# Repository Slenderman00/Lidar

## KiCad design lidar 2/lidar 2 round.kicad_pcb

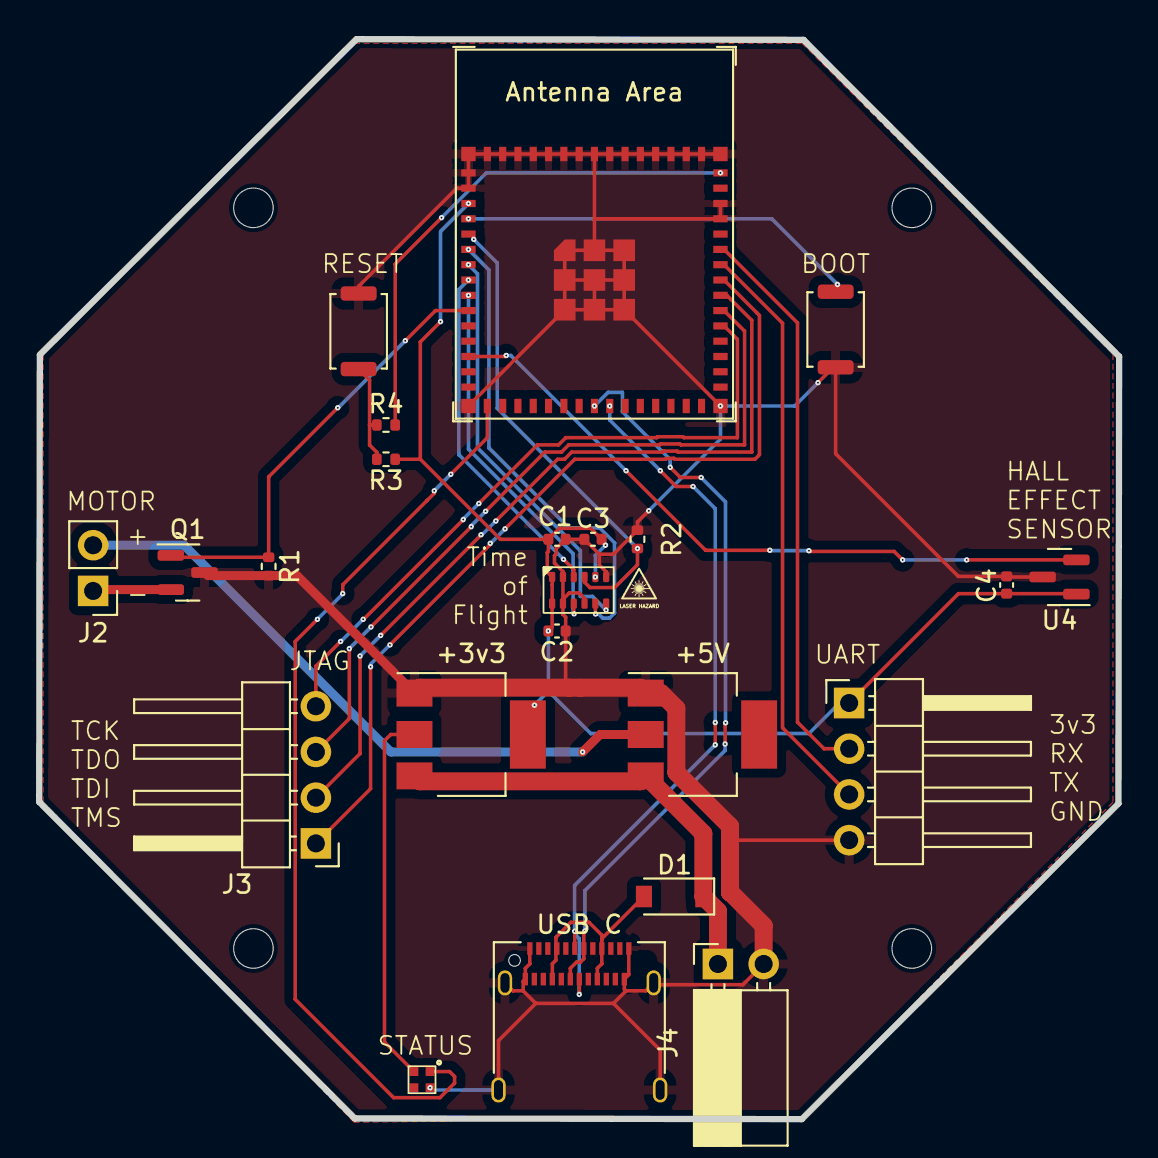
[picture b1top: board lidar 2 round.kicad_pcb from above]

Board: 2 copper layers, 60.0 x 60.0 mm, 27 parts (0 on the bottom side), 25 nets.

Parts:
+3v3: AMS1117-3.3; SOT-223-3_TabPin2
+5V: AMS1117-5.0; SOT-223-3_TabPin2
C1, C2, C3, C4: X7R 0.1 μF 6.3 V; C_0402_1005Metric
D1: MBR0520; D_SOD-123
H1, H2, H3, H5: MountingHole_Pad; MountingHole_2.2mm_M2
J1: UART; PinHeader_1x04_P2.54mm_Horizontal
J2: Motor; PinHeader_1x02_P2.54mm_Vertical
J3: JTAG; PinHeader_1x04_P2.54mm_Horizontal
J4: VIN; PinSocket_1x02_P2.54mm_Horizontal
Q1: BC847; SOT-23
R1, R2: 1Mohm; R_0402_1005Metric
R3, R4: 1 Mohm; R_0402_1005Metric
SW1: BOOT; SW_Push_SPST_NO_Alps_SKRK
SW2: RESET; SW_Push_SPST_NO_Alps_SKRK
U2: TMF8805
U3: LC8805B-1515
U4: DRV5055A2xDBZxQ1; SOT-23
U5: ESP32-S3-MINI-1
USB C: USB_C_Receptacle_USB2.0; USB_C_Receptacle_Amphenol_12401610E4-2A

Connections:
+3.3V: +3v3.2 (VO), C1.2, C2.2, C3.2, C4.2, J1.1, R3.1, U2.1 (VDDV), U2.8 (GND), U2.12 (VDDC), U3.2 (VDD), U4.1 (VCC), U5.3 (3V3)
+5V: +5V.2 (VO), J2.2
D+: U5.24 (GPIO20/U1CTS/ADC2_CH9/CLK_OUT1/USB_D+), USB C.A6 (D+), USB C.B6 (D+)
D-: U5.23 (GPIO19/U1RTS/ADC2_CH8/CLK_OUT2/USB_D-), USB C.A7 (D-), USB C.B7 (D-)
Enable: R2.1, U2.9 (EN), U5.5 (GPIO1/TOUCH1/ADC1_CH0)
Enable_Motor: Q1.1 (B), R1.1, U5.10 (GPIO6/TOUCH6/ADC1_CH5)
GND: +3v3.1 (GND), +5V.1 (GND), C1.1, C2.1, C3.1, C4.1, J1.4, J4.2, Q1.3 (C), R1.2, R2.2, SW1.1, SW2.2, U2.2 (GNDC), U2.4 (INT), U2.7 (VDD), U2.11 (GNDV), U3.4 (GND), U4.3 (GND), U5.1 (GND), U5.2 (GND), U5.42 (GND), U5.43 (GND), U5.46 (GND), U5.47 (GND), U5.48 (GND), U5.49 (GND), U5.50 (GND), U5.51 (GND), U5.52 (GND), U5.53 (GND), U5.54 (GND), U5.55 (GND), U5.56 (GND), U5.57 (GND), U5.58 (GND), U5.59 (GND), U5.60 (GND), U5.61 (GND), U5.62 (GND), U5.63 (GND), U5.64 (GND), U5.65 (GND), USB C.A1 (GND), USB C.A12 (GND), USB C.B1 (GND), USB C.B12 (GND), USB C.S1 (SHIELD)
GPIO0: U2.10 (GPIO1), U5.8 (GPIO4/TOUCH4/ADC1_CH3)
GPIO1: U2.3 (GPIO0), U5.9 (GPIO5/TOUCH5/ADC1_CH4)
Hall_Effect_Sensor: U4.2 (OUT), U5.13 (GPIO9/TOUCH9/ADC1_CH8/FSPIHD/SUBSPIHD)
unnamed: D1.2 (A), USB C.A4 (VBUS), USB C.A9 (VBUS), USB C.B4 (VBUS), USB C.B9 (VBUS)
unnamed: J2.1, Q1.2 (E)
unnamed: R3.2, R4.1, SW2.1
unnamed: R4.2, U5.45 (EN)
unnamed: SW1.2, U5.4 (GPIO0/BOOT)
RX: J1.2, U5.40 (U0RXD/GPIO44/CLK_OUT2)
SCL: U2.5 (SCL), U5.6 (GPIO2/TOUCH2/ADC1_CH1)
SDA: U2.6 (SDA), U5.7 (GPIO3/TOUCH3/ADC1_CH2)
SLED: U3.1 (DIN), U5.16 (GPIO12/TOUCH12/ADC2_CH1/FSPICLK/FSPIIO6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)
TCK: J3.4, U5.35 (MTCK/GPIO39/CLK_OUT3/SUBSPICS1)
TDI: J3.2, U5.37 (MTDI/GPIO41/CLK_OUT1)
TDO: J3.3, U5.36 (MTDO/GPIO40/CLK_OUT2)
TMS: J3.1, U5.38 (MTMS/GPIO42)
TX: J1.3, U5.39 (U0TXD/GPIO43/CLK_OUT1)
VIN: +3v3.3 (VI), +5V.3 (VI), D1.1 (K), J4.1

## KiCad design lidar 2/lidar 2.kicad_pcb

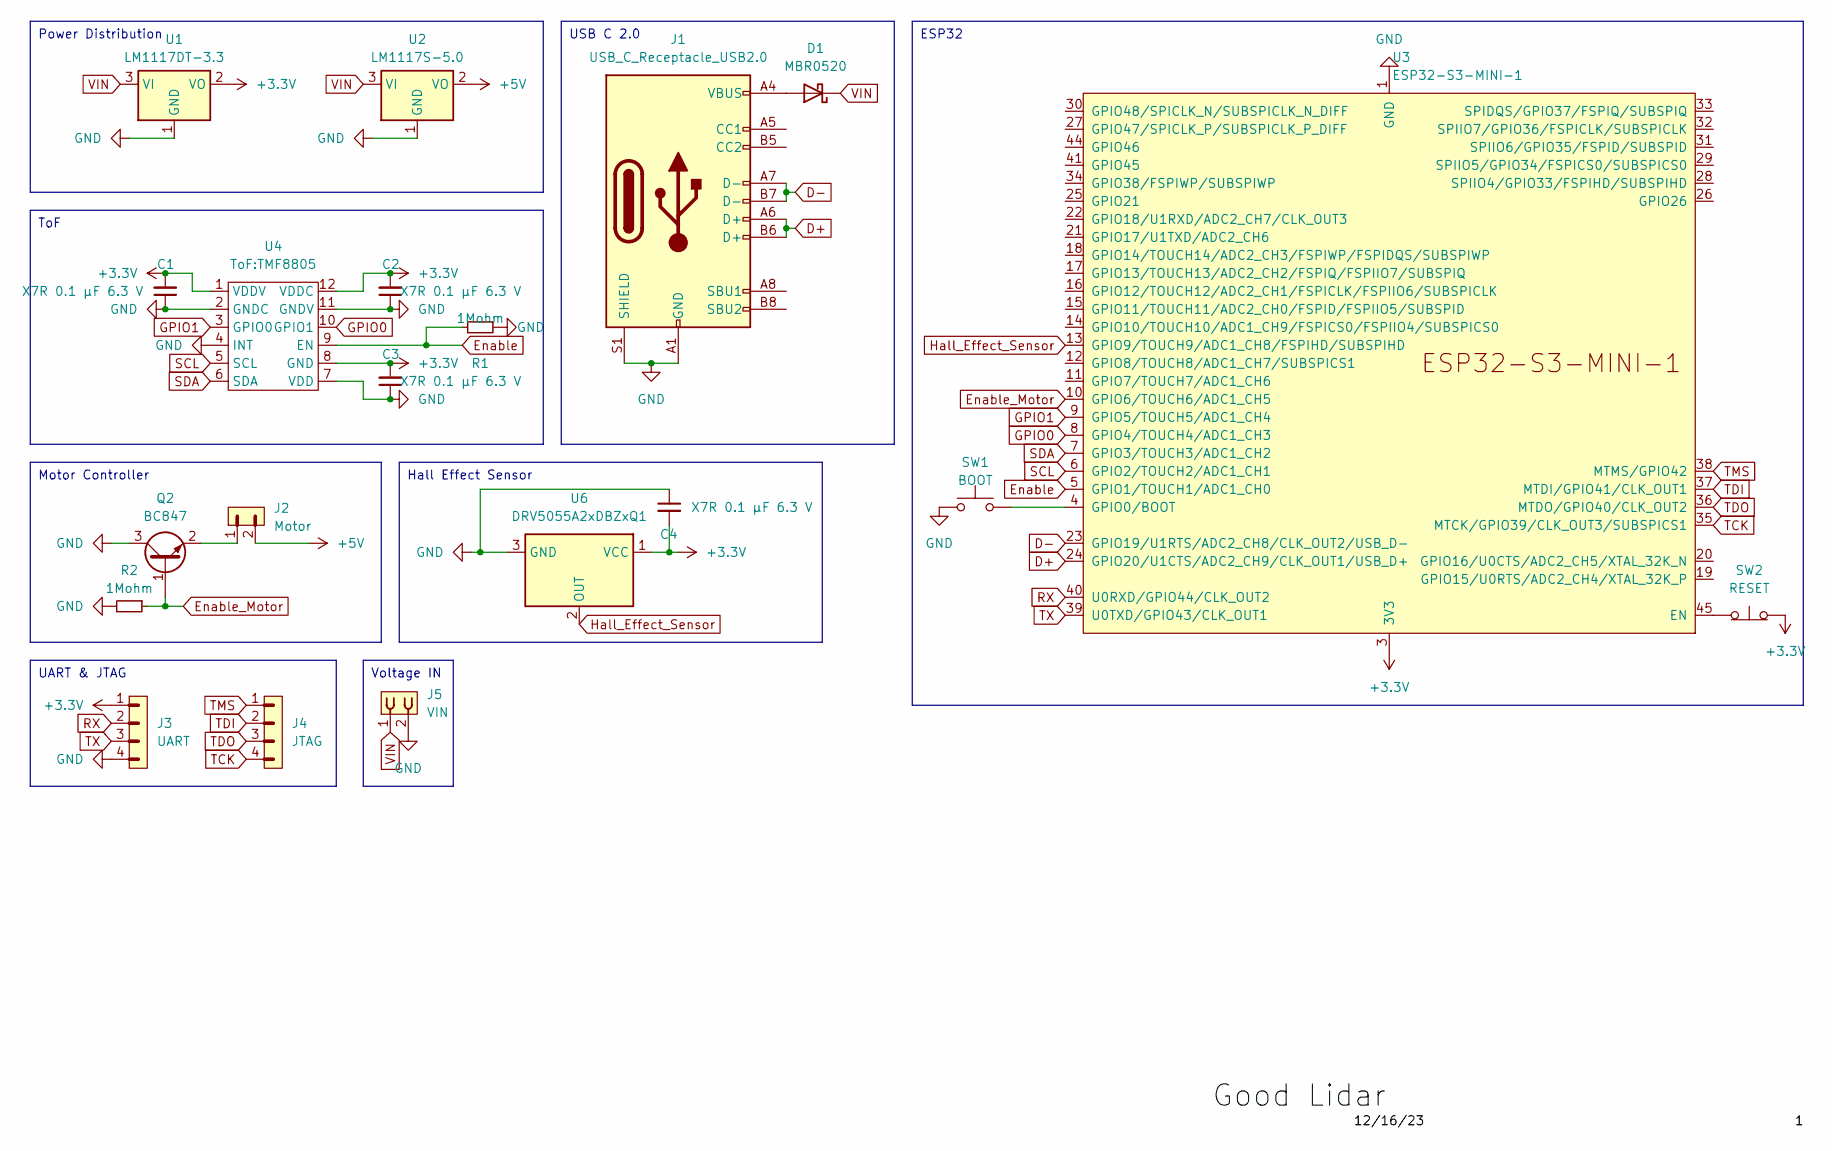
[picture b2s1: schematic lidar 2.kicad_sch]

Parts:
C1, C2, C3, C4: X7R 0.1 μF 6.3 V; C_0402_1005Metric
D1: MBR0520; D_SOD-123
J1: USB_C_Receptacle_USB2.0; USB_C_Receptacle_GCT_USB4110
J2: Motor; PinHeader_1x02_P2.54mm_Vertical
J3: UART; PinHeader_1x04_P2.54mm_Vertical
J4: JTAG; PinHeader_1x04_P2.54mm_Vertical
J5: VIN; PinSocket_1x02_P2.54mm_Vertical
Q2: BC847; SOT-23
R1, R2: 1Mohm; R_0805_2012Metric
SW1: BOOT; SW_Push_1P1T_NO_6x6mm_H9.5mm
SW2: RESET; SW_Push_1P1T_NO_6x6mm_H9.5mm
U1: LM1117DT-3.3; TO-252-3_TabPin2
U2: LM1117S-5.0; TO-263-3_TabPin2
U3: ESP32-S3-MINI-1
U4: TMF8805
U6: DRV5055A2xDBZxQ1; SOT-23

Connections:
+3.3V: C1.2, C2.2, C3.2, C4.2, J3.1, SW2.2 (B), U1.2 (VO), U3.3 (3V3), U4.1 (VDDV), U4.8 (GND), U4.12 (VDDC), U6.1 (VCC)
+5V: J2.2, U2.2 (VO)
D+: J1.A6 (D+), J1.B6 (D+), U3.24 (GPIO20/U1CTS/ADC2_CH9/CLK_OUT1/USB_D+)
D-: J1.A7 (D-), J1.B7 (D-), U3.23 (GPIO19/U1RTS/ADC2_CH8/CLK_OUT2/USB_D-)
Enable: R1.1, U3.5 (GPIO1/TOUCH1/ADC1_CH0), U4.9 (EN)
Enable_Motor: Q2.1 (B), R2.1, U3.10 (GPIO6/TOUCH6/ADC1_CH5)
GND: C1.1, C2.1, C3.1, C4.1, J1.A1 (GND), J1.A12 (GND), J1.B1 (GND), J1.B12 (GND), J1.S1 (SHIELD), J3.4, J5.2, Q2.3 (C), R1.2, R2.2, SW1.1, U1.1 (GND), U2.1 (GND), U3.1 (GND), U3.2 (GND), U3.42 (GND), U3.43 (GND), U3.46 (GND), U3.47 (GND), U3.48 (GND), U3.49 (GND), U3.50 (GND), U3.51 (GND), U3.52 (GND), U3.53 (GND), U3.54 (GND), U3.55 (GND), U3.56 (GND), U3.57 (GND), U3.58 (GND), U3.59 (GND), U3.60 (GND), U3.61 (GND), U3.62 (GND), U3.63 (GND), U3.64 (GND), U3.65 (GND), U4.2 (GNDC), U4.4 (INT), U4.7 (VDD), U4.11 (GNDV), U6.3 (GND)
GPIO0: U3.8 (GPIO4/TOUCH4/ADC1_CH3), U4.10 (GPIO1)
GPIO1: U3.9 (GPIO5/TOUCH5/ADC1_CH4), U4.3 (GPIO0)
Hall_Effect_Sensor: U3.13 (GPIO9/TOUCH9/ADC1_CH8/FSPIHD/SUBSPIHD), U6.2 (OUT)
unnamed: D1.2 (A), J1.A4 (VBUS), J1.A9 (VBUS), J1.B4 (VBUS), J1.B9 (VBUS)
unnamed: J2.1, Q2.2 (E)
unnamed: SW2.1 (A), U3.45 (EN)
unnamed: SW1.2, U3.4 (GPIO0/BOOT)
RX: J3.2, U3.40 (U0RXD/GPIO44/CLK_OUT2)
SCL: U3.6 (GPIO2/TOUCH2/ADC1_CH1), U4.5 (SCL)
SDA: U3.7 (GPIO3/TOUCH3/ADC1_CH2), U4.6 (SDA)
TCK: J4.4, U3.35 (MTCK/GPIO39/CLK_OUT3/SUBSPICS1)
TDI: J4.2, U3.37 (MTDI/GPIO41/CLK_OUT1)
TDO: J4.3, U3.36 (MTDO/GPIO40/CLK_OUT2)
TMS: J4.1, U3.38 (MTMS/GPIO42)
TX: J3.3, U3.39 (U0TXD/GPIO43/CLK_OUT1)
VIN: D1.1 (K), J5.1, U1.3 (VI), U2.3 (VI)

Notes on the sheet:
Power Distribution
USB C 2.0
Hall Effect Sensor
UART & JTAG
ToF
ESP32
Voltage IN
Motor Controller

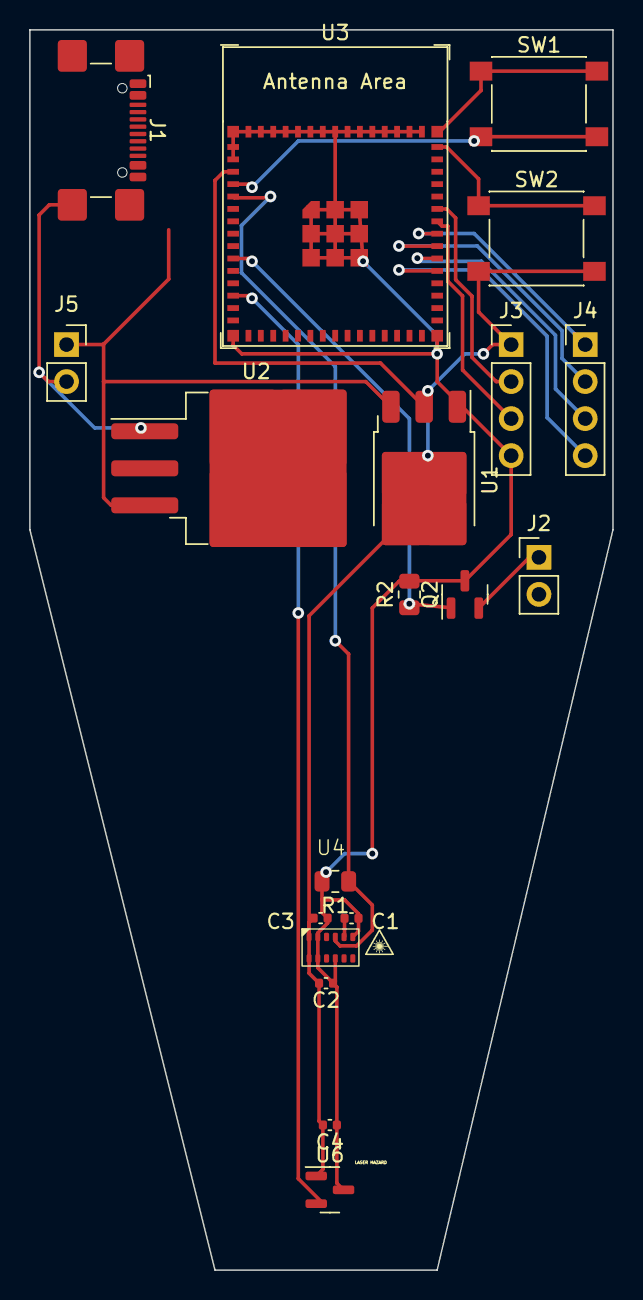
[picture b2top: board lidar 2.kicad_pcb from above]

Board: 2 copper layers, 40.0 x 85.1 mm, 19 parts (0 on the bottom side), 23 nets.

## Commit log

2023-12-19 Added fusion 360 archive
2023-12-21 Made some changes
2023-12-21 More changes
2023-12-21 Finsished mk2
